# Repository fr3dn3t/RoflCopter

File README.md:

# RoflCopter
My RoflCopter makes swush swush swush - just kidding. The RoflCopter a monocopter, monospinner, gyropter, drone whatever you want to call it. 

I'm working on this project since October 2015 and until now, there have been two versions. The first Version was built to test various parameters and hardware approaches to make it fly - Version 1 was completed in May 2016, but never flew.
Applying the lessons learned from the first version I started to build a secont one. This one was completly designed via CAD and the rotor blades were simulated in XFLR5. A full documentation can be found in V2/docs/ (german only), the first successful flight was on 14th February 2017 [Video](https://github.com/fr3dn3t/RoflCopter/blob/master/V2/videos/RoflCopter%20-%20FirstFlight14022017.mp4)

more to come

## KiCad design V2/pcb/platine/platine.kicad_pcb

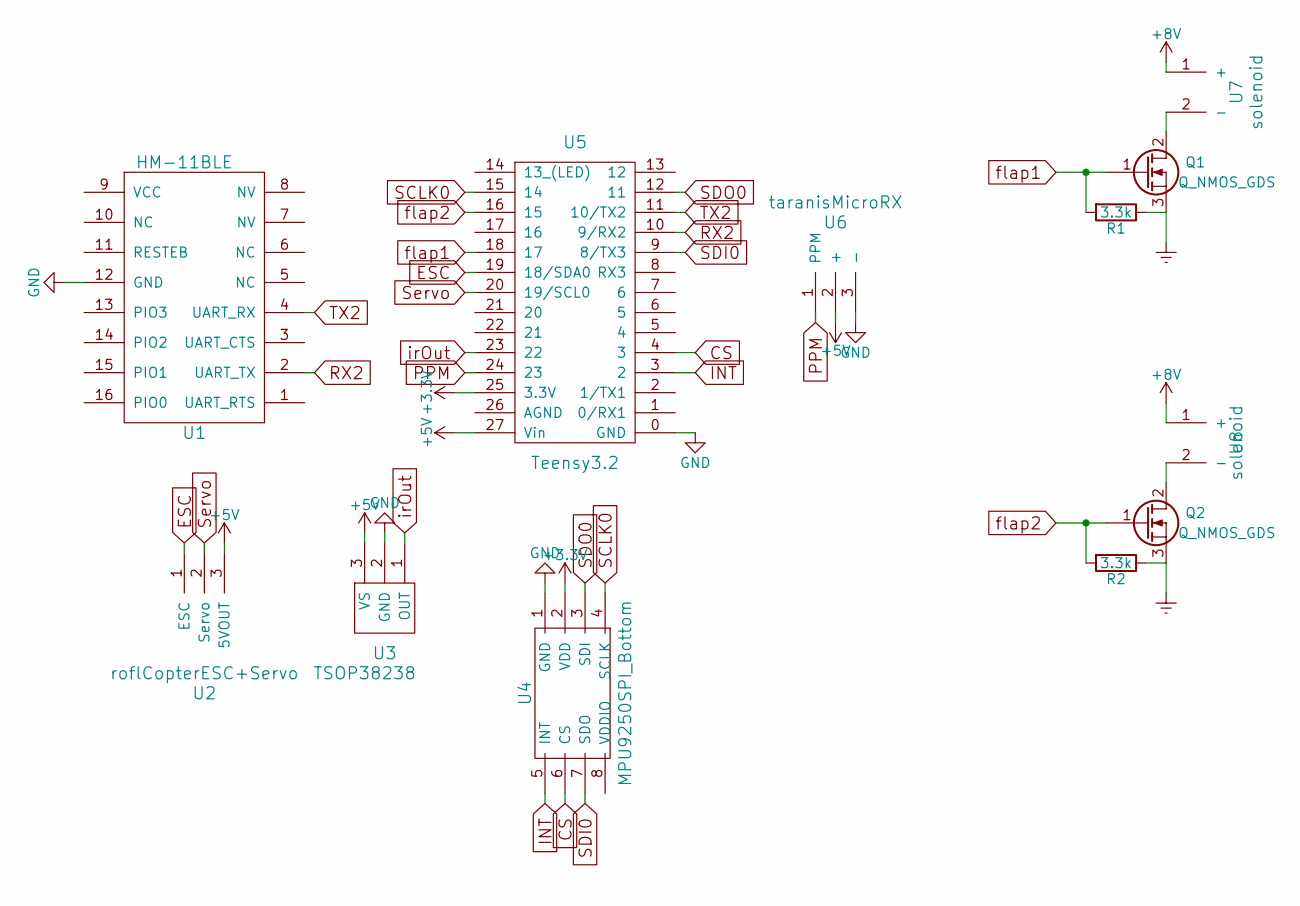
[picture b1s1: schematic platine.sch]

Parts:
Q1, Q2: Q_NMOS_GDS; TO-252-2Lead
R1, R2: 3.3k; R_1206_HandSoldering
U1: HM-11BLE; HM-11ble
U2: roflCopterESC+Servo
U3: TSOP38238
U4: MPU9250SPI_Bottom; MPU9250SPI_BOTTOM
U5: Teensy3.2; Teensy3.2_l
U6: taranisMicroRX
U7, U8: solenoid

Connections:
+3V3: U4.2 (VDD), U5.25 (3.3V)
+5V: U2.3 (5VOUT), U3.3 (VS), U5.27 (Vin), U6.2 (+)
+8V: U7.1 (+), U8.1 (+)
CS: U4.6 (CS), U5.4 (3)
ESC: U2.1 (ESC), U5.19 (18/SDA0)
Earth: Q1.3 (S), Q2.3 (S), R1.1, R2.1
GND: U1.12 (GND), U3.2 (GND), U4.1 (GND), U5.0 (GND), U6.3 (-)
INT: U4.5 (INT), U5.3 (2)
unnamed: Q1.2 (D), U7.2 (-)
unnamed: Q2.2 (D), U8.2 (-)
PPM: U5.24 (23), U6.1 (PPM)
RX2: U1.2 (UART_TX), U5.10 (9/RX2)
SCLK0: U4.4 (SCLK), U5.15 (14)
SDI0: U4.7 (SDO), U5.9 (8/TX3)
SDO0: U4.3 (SDI), U5.12 (11)
Servo: U2.2 (Servo), U5.20 (19/SCL0)
TX2: U1.4 (UART_RX), U5.11 (10/TX2)
flap1: Q1.1 (G), R1.2, U5.18 (17)
flap2: Q2.1 (G), R2.2, U5.16 (15)
irOut: U3.1 (OUT), U5.23 (22)

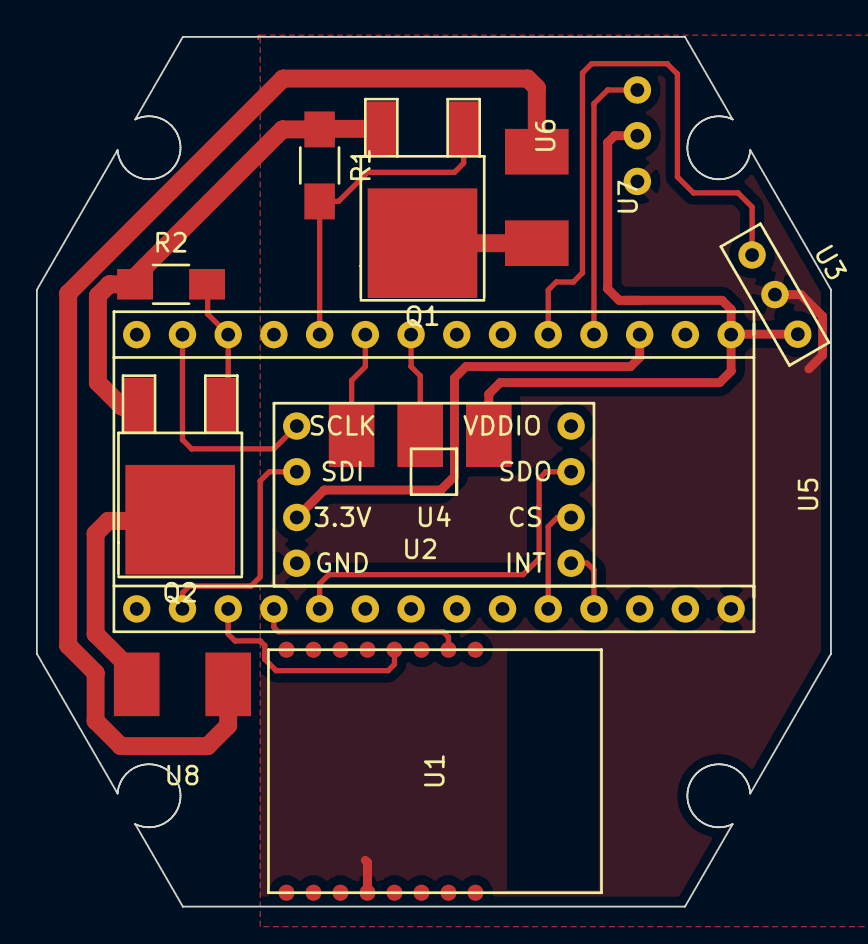
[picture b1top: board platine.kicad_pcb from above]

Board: 2 copper layers, 44.1 x 48.3 mm, 12 parts (0 on the bottom side), 20 nets.

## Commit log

2017-02-08 finally uploaded something; first commit
2017-02-08 changed imu examples and added first version of a framework
2017-02-08 changed some imu files
2017-02-08 added Framework including the functions for all hardware modules
2017-02-08 removed Framework
2017-02-08 added Framework including functions for the hardware
2017-02-08 added first version of a landing secuence and added continious intervall timer controlled servo control to the framework
2017-02-11 continued on Framework
2017-02-11 added various debug messeges to the framework
2017-02-11 speeded up emergency stop
2017-02-11 interupts are disabled at emergency stop
2017-02-12 changes the initial speed of the motors and increased the servo slew distances
2017-02-12 added rpm calculation and debug buffer
2017-02-13 changed Framework parameters and edited the ble com file
2017-02-15 added imu-value-visualizer(not working yet), changed the HWSERIAL Routine (two HM-11 BLE modules pared)
2017-02-15 added new images
2017-02-15 added video of the first successful flight on 14.02.2017
2017-02-15 worked on debug Graph software
2017-02-16 finished debug visualisation software and paired the two hm11 ble modules
2017-02-16 finished the debugGraph Software, added temporary debug functionality to the framework
2017-02-17 added firmware for the presentation of the different functions - not working yet
2017-02-23 fixed esc test firmware; was mixed up with servo test firmware
2017-02-23 added ir blinder angle measurement test firmware
2017-02-23 added image of the presentation flight at Jugendforscht Münster 17.02.2017
2017-02-23 rotated image
2017-02-24 updated the complete report about version 2
2017-02-24 uploaded final version of the report
2017-04-02 added point transformation for the control algorithm
2017-05-11 modified presentation mode and flap tests
2017-05-11 new version of the paper about the roflCopter
2017-05-12 firmware to determine the angle between the copter and pilot when IR is recieved
2017-05-12 testing new control algorithm debug foo
2017-05-12 more detailes debug logs and reduced baud rate to reduce debug log transmission errors
2017-05-13 static motor control and more logging foo
2017-05-14 added landing sequence
2017-05-14 checked landing foo
2017-05-14 modified flap test firmware for use with slowmotion video analysis to determine the flap's speed
2017-05-15 activated the control loop for debug purposes
2017-05-16 fixed rx ppm fail (sync break wasn't always >8ms)
2017-05-16 fixed the motor start serial error
2017-05-16 changed everything to single precision, since it is enough
2017-05-16 reviewed the angle functions; encountered some problems which will be fixed tomorrow
2017-05-16 fixed angle calculation problem by converting the rad value to degree...
2017-05-17 fixed the results of my mathematical stupidness
2017-05-22 changed the speed parameter for the motor control
2017-05-22 finetuned the motor speed
2017-05-22 tested the hardware timer to control the flaps
2017-05-22 included the hardwartimer flap control into the flight firmware
2017-08-24 add slowmotion test firmware
2017-08-24 extended flap control test
2017-08-24 include flap time differences and scaled the control angle up
2017-10-24 add latest scad file
2017-10-24 add screwprop scad file which is a dependency of the latest scad file of the model
2017-10-24 Version 3!! \o/
2017-10-24 add screwprop file which is a dependency of the model files
2017-10-24 update design of model (switched Teensy 3.2 to DIPFORTy1 by TrezElectronic) and add NACA0009 to rotor design project
2017-10-25 just some design experiments
2017-10-25 add naca profiles
2017-10-25 rotorblade vortex analysis
